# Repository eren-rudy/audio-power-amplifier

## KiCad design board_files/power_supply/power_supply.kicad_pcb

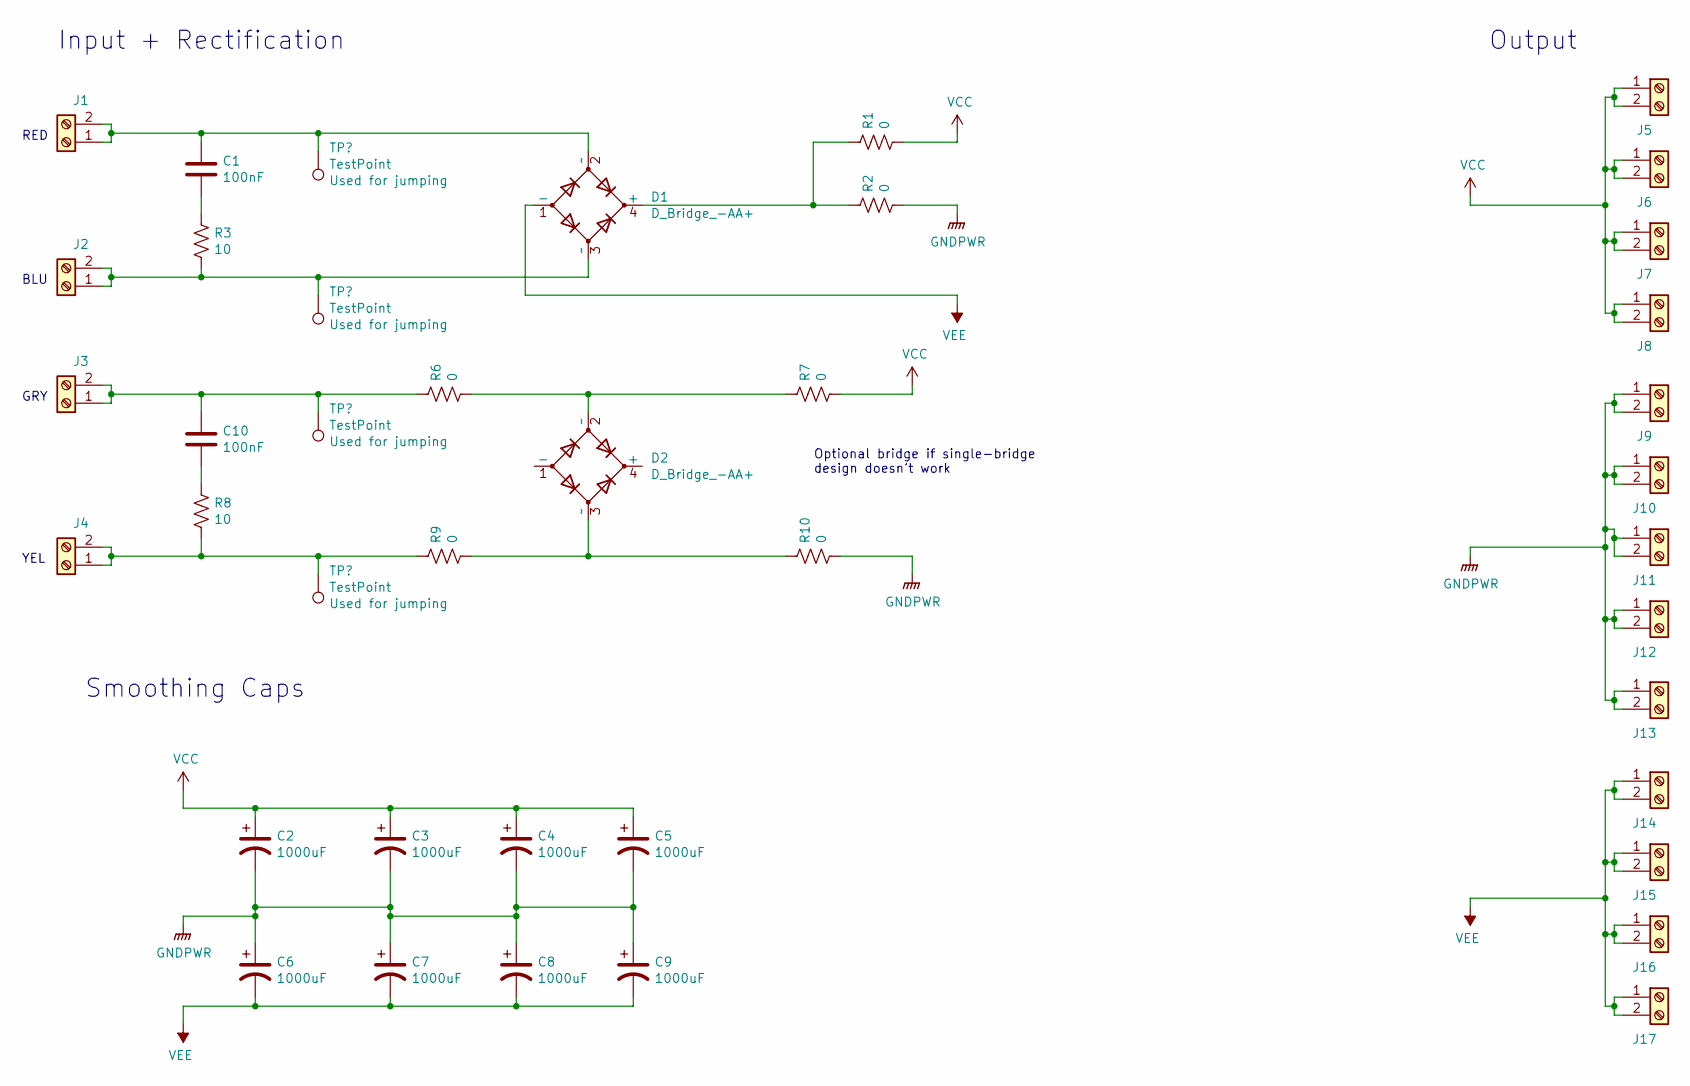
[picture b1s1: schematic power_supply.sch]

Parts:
C1, C10: 100nF; C_1206_3216Metric; MPN 885012208118; Digikey PN 732-12245-1-ND
C2, C3, C4, C5, C6, C7, C8, C9: 1000uF; CP_Radial_D12.5mm_P5.00mm; MPN ECA-1HM102B; Digikey PN P19529CT-ND
D1, D2: D_Bridge_-AA+; Diode_Bridge_32.0x5.6x17.0mm_P10.0mm_P7.5mm; MPN GBJ2508-BP; Digikey PN GBJ2508-BPMS-ND
J1, J2, J3, J4, J5, J6, J7, J8, J9, J10, J11, J12, J13, J14, J15, J16, J17: Screw_Terminal_01x02; TE_QC_250_Male_Blade_P5.08; MPN 1217861-1; Digikey PN A100452CT-ND
R1, R2, R6, R7, R9, R10: 0; 12_Gauge_Jumper
R3, R8: 10; R_Axial_DIN0207_L6.3mm_D2.5mm_P7.62mm_Horizontal; MPN FMP100JR-52-10R; Digikey PN 10WCT-ND

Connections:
GNDPWR: C2.2, C3.2, C4.2, C5.2, C6.1, C7.1, C8.1, C9.1, J9.1, J9.2, J10.1, J10.2, J11.1, J11.2, J12.1, J12.2, J13.1, J13.2, R2.2, R10.2
unnamed 1: C1.1, D1.2 (~~), J1.1, J1.2; also elsewhere on the board
unnamed: C1.2, R3.1
unnamed 3: C10.1, J3.1, J3.2, R6.1; also elsewhere on the board
unnamed: C10.2, R8.1
unnamed 5: D1.3 (~~), J2.1, J2.2, R3.2; also elsewhere on the board
unnamed: D1.4 (+), R1.1, R2.1
unnamed: D2.2 (~~), R6.2, R7.1
unnamed: D2.3 (~~), R9.2, R10.1
unnamed 11: J4.1, J4.2, R8.2, R9.1; also elsewhere on the board
VCC: C2.1, C3.1, C4.1, C5.1, J5.1, J5.2, J6.1, J6.2, J7.1, J7.2, J8.1, J8.2, R1.2, R7.2
VEE: C6.2, C7.2, C8.2, C9.2, D1.1 (-), J14.1, J14.2, J15.1, J15.2, J16.1, J16.2, J17.1, J17.2

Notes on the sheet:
RED
BLU
GRY
YEL
Optional bridge if single-bridge design doesn’t work
Input + Rectification
Smoothing Caps
Output

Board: 2 copper layers, 41 parts (0 on the bottom side), 12 nets, no tracks yet.

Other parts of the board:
TP1, TP2, TP3, TP4: TestPoint; 12_Gauge_Jumper_one_pad

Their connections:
unnamed 1: TP1.1; also elsewhere on the board
unnamed 3: TP3.1; also elsewhere on the board
unnamed 5: TP2.1; also elsewhere on the board
unnamed 11: TP4.1; also elsewhere on the board

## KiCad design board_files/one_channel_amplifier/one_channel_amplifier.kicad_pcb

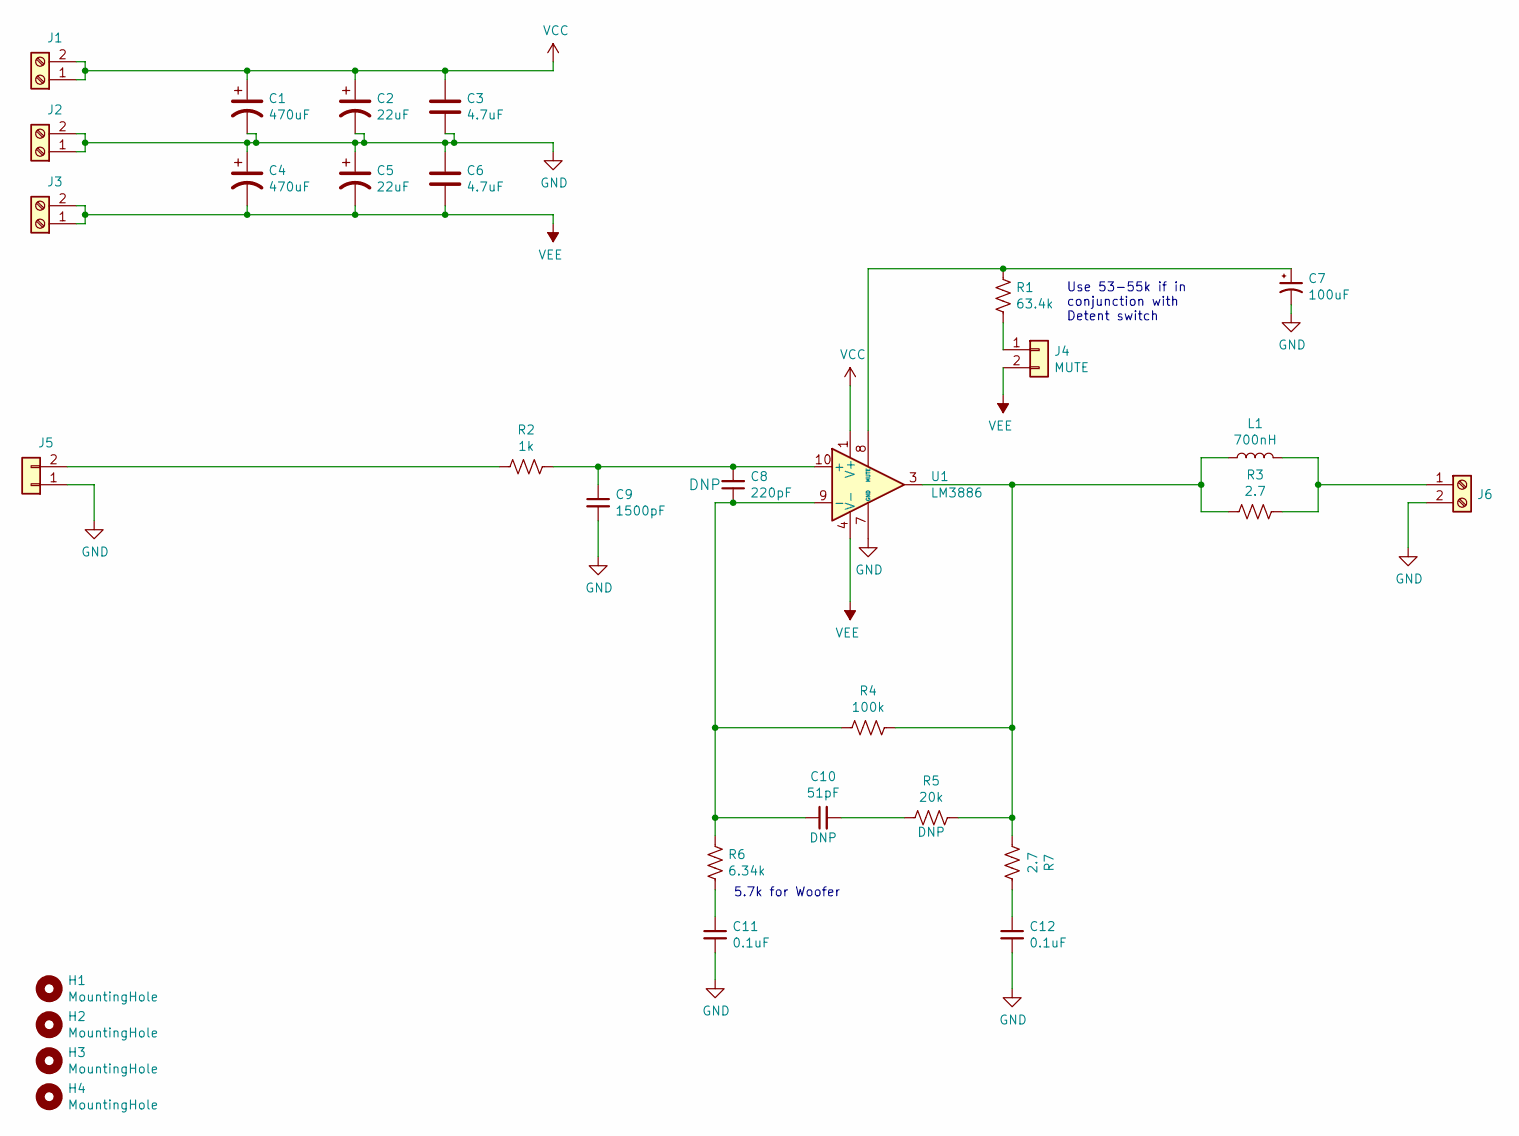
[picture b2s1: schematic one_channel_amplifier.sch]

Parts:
C1, C4: 470uF; CP_Radial_D16.0mm_P7.50mm; MPN ECA-2AHG471B
C2, C5: 22uF; CP_Radial_D10.0mm_P5.00mm; MPN 100SXE22M
C3, C6: 4.7uF; R_1210_3225Metric; MPN CL32B475KCVZW6E
C7: 100uF; CP_Radial_D8.0mm_P3.50mm; MPN ECA-1HM101
C8: 220pF; C_0603_1608Metric; MPN C0603C221K1RACTU; Digikey PN 399-7877-1-ND
C9: 1500pF; C_0603_1608Metric; MPN GRM188R72A152KA01D; Digikey PN 490-1475-1-ND
C10: 51pF; C_0603_1608Metric; MPN CL10C510JB8NNNC
C11, C12: 0.1uF; C_0603_1608Metric; MPN CC0603KRX7R0BB104
H1, H2, H3, H4: MountingHole; MountingHole_3.2mm_M3
J1, J2, J3: Screw_Terminal_01x02; TE_QC_250_Male_Blade_P5.08; MPN 1217861-1; Digikey PN A100452CT-ND
J4, J5: Conn_01x02; PinHeader_1x02_P2.54mm_Vertical
J6: Screw_Terminal_01x02; TerminalBlock_bornier-2_P5.08mm; MPN EB147A-02-D; Digikey PN 2057-EB147A-02-D-ND
L1: PA0277NL; MPN PA0277NL
R1: 63.4k; R_0603_1608Metric; MPN ERJ-3EKF6342V
R2: 1k; R_0603_1608Metric; MPN RC0603FR-071KL; Digikey PN 311-1.00KHRCT-ND
R3, R7: 2.7; R_0603_1608Metric; MPN RK73H1JTTD2R70F; Digikey PN 2019-RK73H1JTTD2R70FCT-ND
R4: 100k; R_0603_1608Metric; MPN RMCF0603FT100K
R5: 20k; R_0603_1608Metric; MPN ERJ-3EKF2002V
R6: 6.34k; R_0603_1608Metric; MPN ERJ-6ENF6341V
U1: LM3886; TO-220F-11_P3.4x5.08mm_StaggerOdd_Lead5.08mm_Vertical; MPN LM3886T/NOPB

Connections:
GND: C1.2, C2.2, C3.2, C4.1, C5.1, C6.1, C7.2, C9.2, C11.2, C12.2, J2.1, J2.2, J5.1, J6.2, U1.7 (GND)
unnamed: C7.1, R1.1, U1.8 (MUTE)
unnamed: C8.2, C9.1, R2.1, U1.10 (+)
unnamed: C8.1, C10.1, R4.2, R6.1, U1.9 (-)
unnamed: C10.2, R5.2
unnamed: C11.1, R6.2
unnamed: C12.1, R7.2
unnamed: J4.1, R1.2
unnamed: J5.2, R2.2
unnamed: J6.1, L1.2, R3.2
unnamed: L1.1, R3.1, R4.1, R5.1, R7.1, U1.3
VCC: C1.1, C2.1, C3.1, J1.1, J1.2, U1.1 (V+), U1.5 (V+)
VEE: C4.2, C5.2, C6.2, J3.1, J3.2, J4.2, U1.4 (V-)

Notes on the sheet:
5.7k for Woofer
Use 53-55k if in conjunction with Detent switch

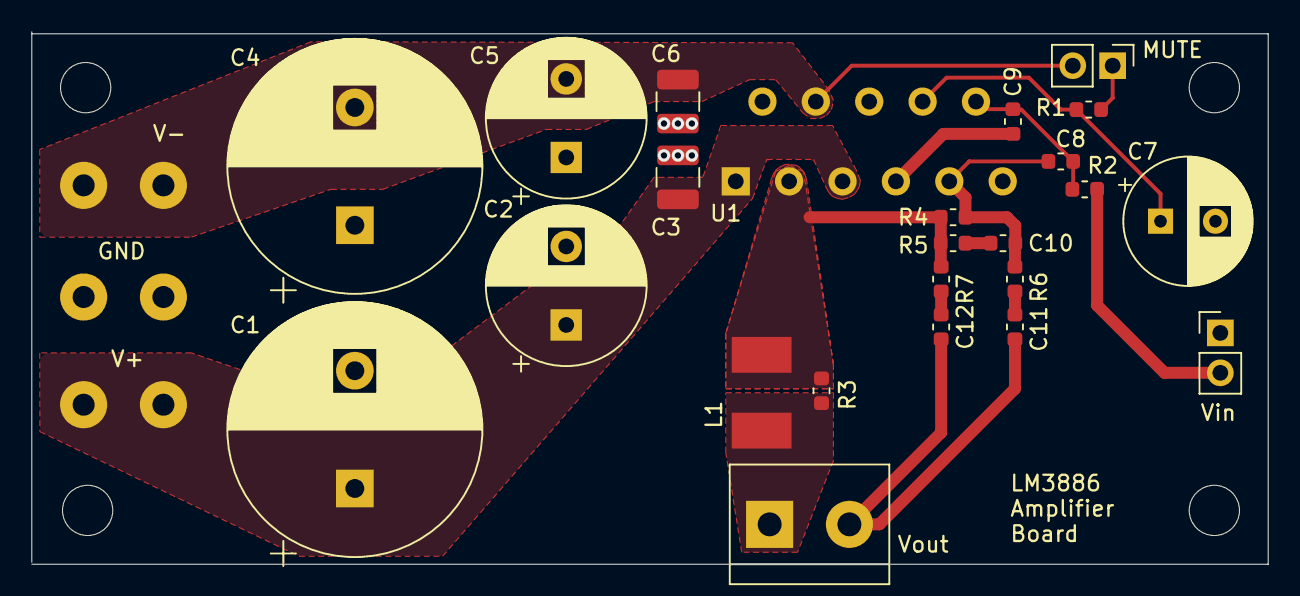
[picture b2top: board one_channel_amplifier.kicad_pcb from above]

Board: 2 copper layers, 78.7 x 33.9 mm, 31 parts (0 on the bottom side), 13 nets.

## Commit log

2018-02-22 Added low-pass filter simulation
2018-02-22 Added SPL calculations
2018-03-11 addded working spice model
2018-03-17 Added power simulation and calculations
2018-03-27 Added Altium PCB project and libraries
2018-03-29 Added simulation and calculations for low pass filter
2018-04-04 Added resistors to library
2018-04-06 Added capacitor library
2018-04-07 Added inductor
2018-04-07 Added 3.5mm connector
2018-04-08 Added Altium schematic
2018-04-08 Finished prototype PCB design
2018-04-09 Added BOM
2018-04-10 Created Gerber X2 outputs
2018-04-14 Added PDF of schematic
2018-04-14 Added schematic PDF
2018-04-20 Adjusted Tweeter design
2018-04-20 Adjusted woofer design
2018-04-21 Added spreadsheet for test cases
2018-04-25 Added sketch of cabinet in SW
2020-05-26 Added initial simulations and screenshots for ideal vs. non-ideal case
2020-05-28 Added folder for simulation results
2020-05-31 Re-organized simulation files and results
2020-06-04 Added total ideal sim and stability sim
2020-06-04 fixed old transformer sim
2020-06-05 Fixed psu model, added model for diode resonance
2020-06-06 added psu circuit with parasitics
2020-06-07 added different psu config sims
2020-06-08 added screenshot of final amplifier schematic
2020-06-09 added kicad project for amplifier board
2020-06-10 added potentiometer to schematic
2020-06-11 added thiele network
2020-06-12 more schematic progress
2020-06-13 finished bypass caps
2020-06-13 fixed image quality
2020-06-14 finished adding components
2020-06-15 finished schematic, started panel BOM
2020-06-16 Finalized sch and exported to layout
2020-06-17 Changed power input to use quick connect plugs
2020-06-18 Initial component placement process
2020-06-21 completed component placement
2020-06-22 added 3rd design iteration
2020-06-23 added power planes
2020-06-25 removed other PCB designs
2020-06-25 removed silkscreen from U1
2020-06-26 Finished first rev
2020-06-27 Added mounting holes to amplifier PCB
2020-06-30 Added bridge rectifiers
2020-07-03 Finished adding components to PSU schematic, started wiring
2020-07-05 finished psu schematic and added front panel
2020-07-08 Started PSU layout + panel
2020-07-10 rough component placement
